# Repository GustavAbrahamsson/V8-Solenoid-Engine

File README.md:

# V8-Solenoid-Engine

See it in action:

https://imgur.com/a/upsOSZD

https://imgur.com/a/mojqysO

https://imgur.com/a/09qQa0Y

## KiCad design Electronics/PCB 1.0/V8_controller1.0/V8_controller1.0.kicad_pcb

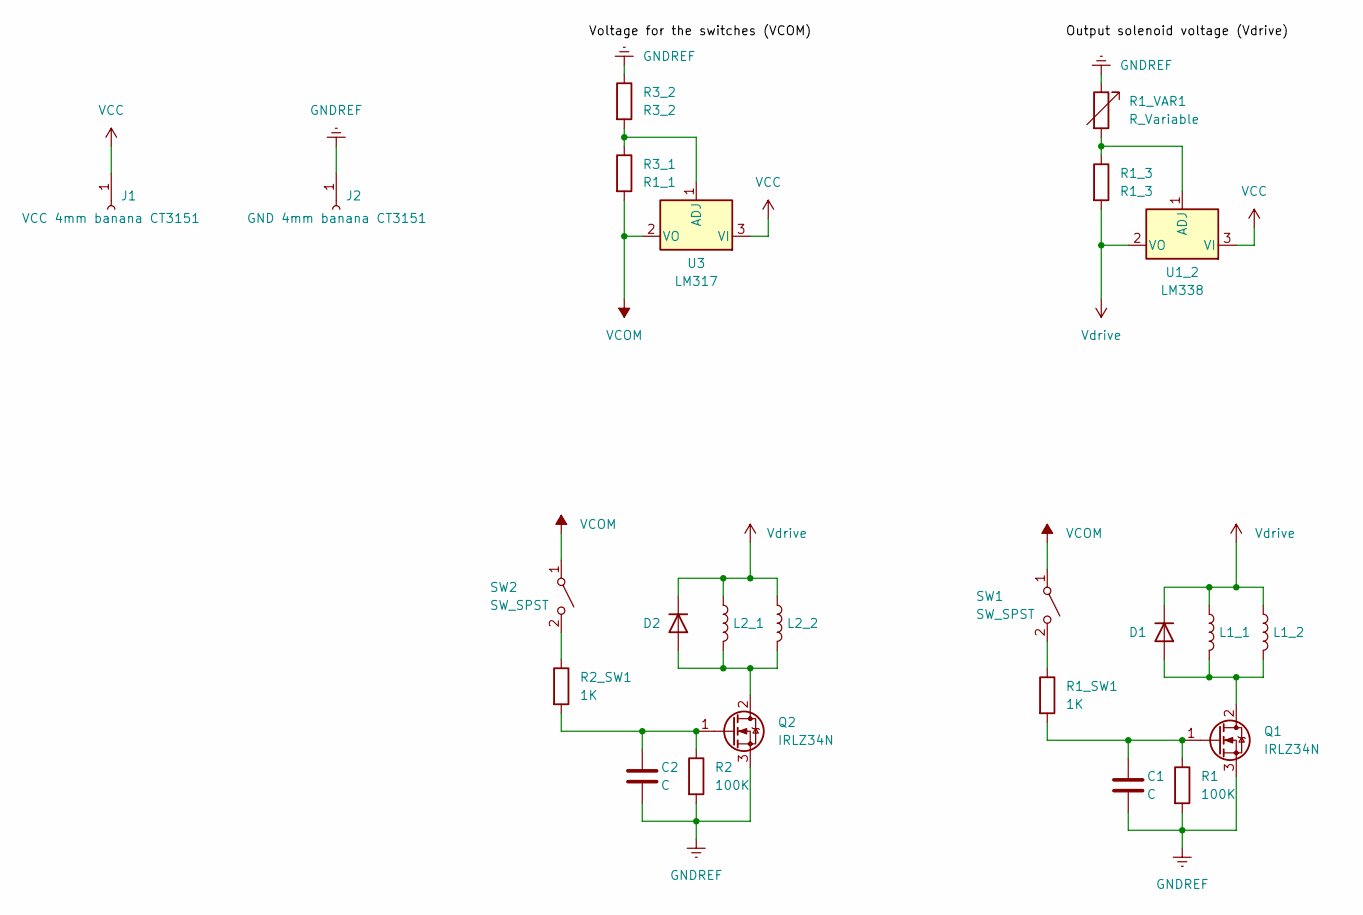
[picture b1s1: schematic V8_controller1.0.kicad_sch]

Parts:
C1, C2: C; R_0805_2012Metric_Pad1.20x1.40mm_HandSolder
D1, D2: DIODE; D_SMA-SMB_Universal_Handsoldering
J1: VCC 4mm banana CT3151; CalTest_CT3151
J2: GND 4mm banana CT3151; CalTest_CT3151
L1_1, L1_2, L2_1, L2_2: L; JST_EH_S2B-EH_1x02_P2.50mm_Horizontal
Q1, Q2: IRLZ34N; TO-220-3_Horizontal_TabDown
R1, R2: 100K; R_0805_2012Metric_Pad1.20x1.40mm_HandSolder
R1_3: R1_3; R_0805_2012Metric_Pad1.20x1.40mm_HandSolder
R1_SW1, R2_SW1: 1K; R_0805_2012Metric_Pad1.20x1.40mm_HandSolder
R1_VAR1: R_Variable; R_Axial_DIN0204_L3.6mm_D1.6mm_P1.90mm_Vertical
R3_1: R1_1; R_0805_2012Metric_Pad1.20x1.40mm_HandSolder
R3_2: R3_2; R_0805_2012Metric_Pad1.20x1.40mm_HandSolder
SW1, SW2: SW_SPST; JST_EH_S2B-EH_1x02_P2.50mm_Horizontal
U1_2: LM338; TO-220-3_Horizontal_TabDown
U3: LM317; TO-263-2

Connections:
GNDREF: C1.2, C2.2, J2.1, Q1.3 (S), Q2.3 (S), R1.2, R1_VAR1.1, R2.2, R3_2.1
unnamed: C1.1, Q1.1 (G), R1.1, R1_SW1.2
unnamed: C2.1, Q2.1 (G), R2.1, R2_SW1.2
unnamed: D1.1 (A), L1_1.2, L1_2.2, Q1.2 (D)
unnamed: D2.1 (A), L2_1.2, L2_2.2, Q2.2 (D)
unnamed: R1_3.1, R1_VAR1.2, U1_2.1 (ADJ)
unnamed: R1_SW1.1, SW1.2 (B)
unnamed: R2_SW1.1, SW2.2 (B)
unnamed: R3_1.1, R3_2.2, U3.1 (ADJ)
VCC: J1.1, U1_2.3 (VI), U3.3 (VI)
VCOM: R3_1.2, SW1.1 (A), SW2.1 (A), U3.2 (VO)
Vdrive: D1.2 (K), D2.2 (K), L1_1.1, L1_2.1, L2_1.1, L2_2.1, R1_3.2, U1_2.2 (VO)

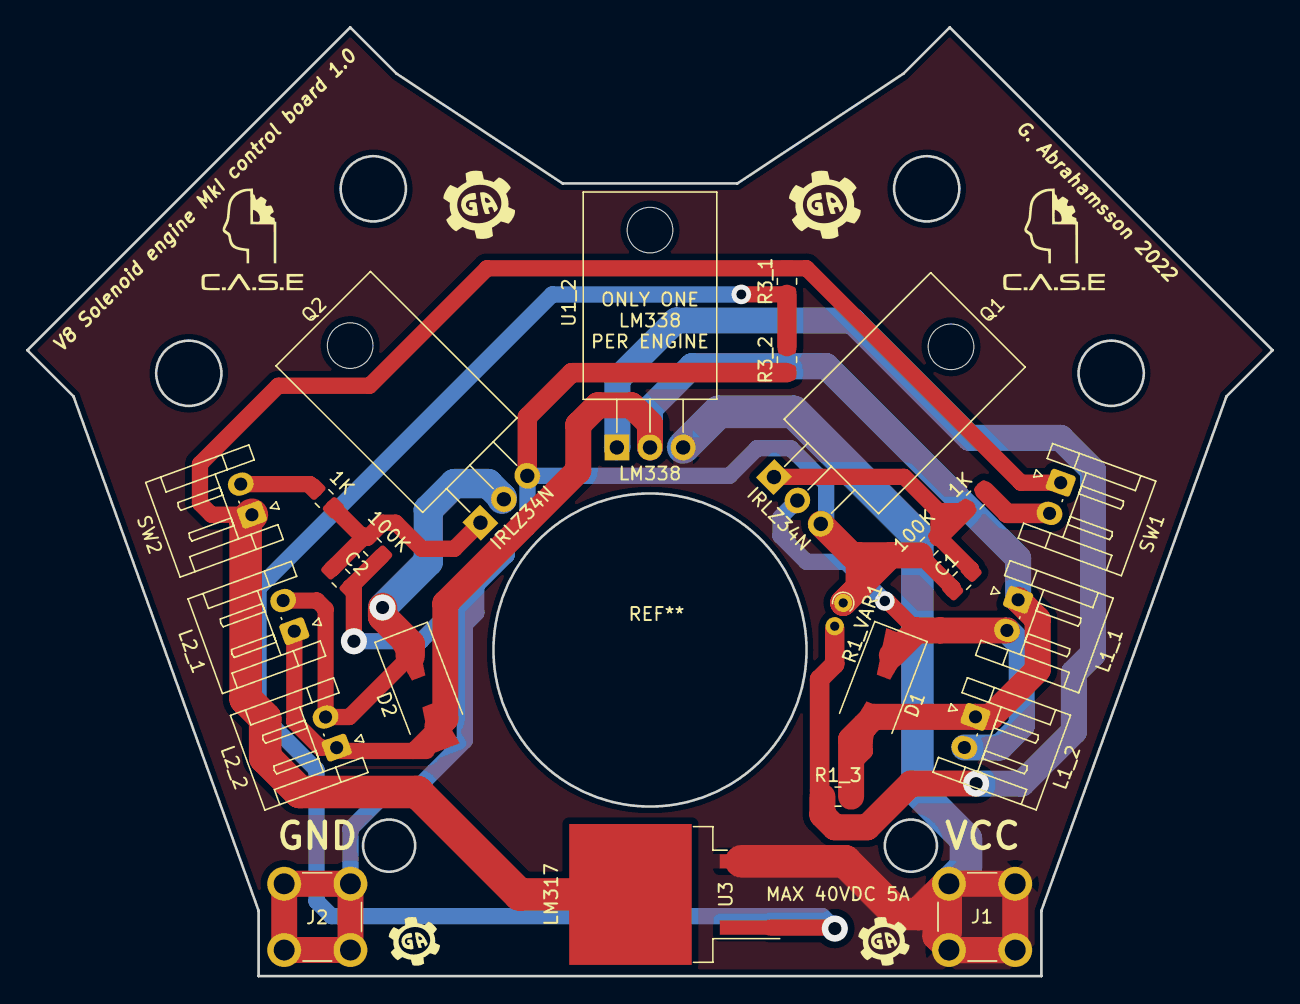
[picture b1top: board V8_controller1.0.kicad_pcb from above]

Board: 2 copper layers, 95.5 x 72.7 mm, 24 parts (0 on the bottom side), 12 nets.

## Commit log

2022-09-09 Init
2022-10-04 Add KiCad project
2022-10-05 Add voltage control with extra LM317
2022-10-06 Add CAD
2022-10-11 Add final gerberfiles for 1.0
2022-10-12 Add updated cylinder frame drawing
2022-10-26 Add improvement list
2022-10-27 Sync
2022-11-08 Update improvements
2022-12-07 Add pictures
